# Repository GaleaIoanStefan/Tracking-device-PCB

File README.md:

# Project description

In this project i have designed and coded a shield for the STM32 Nucleo board L476RG.

The shield is the prototype of a tracker that will update the position using a GPS module and a LoRa modem for communication with a server.
The board is made to connect to the Orange LiveObjects server from which the data is put inside a MongoDB database and later a template is made in Grafana with the longitude and latitude coordinates.
Two Python scripts are present in the project. One for getting the data from the LiveObjects through MQTT protocol, and the other links the data received to a endpoint. That endpoint in later linked to a Grafana JSON plugin to gather that data.

The programming of the board was done in STM32CubeIDE and all communications between The GPS, Lora and COM port were UART communications.

# The Electrical Schematic

# The layout of the PCB

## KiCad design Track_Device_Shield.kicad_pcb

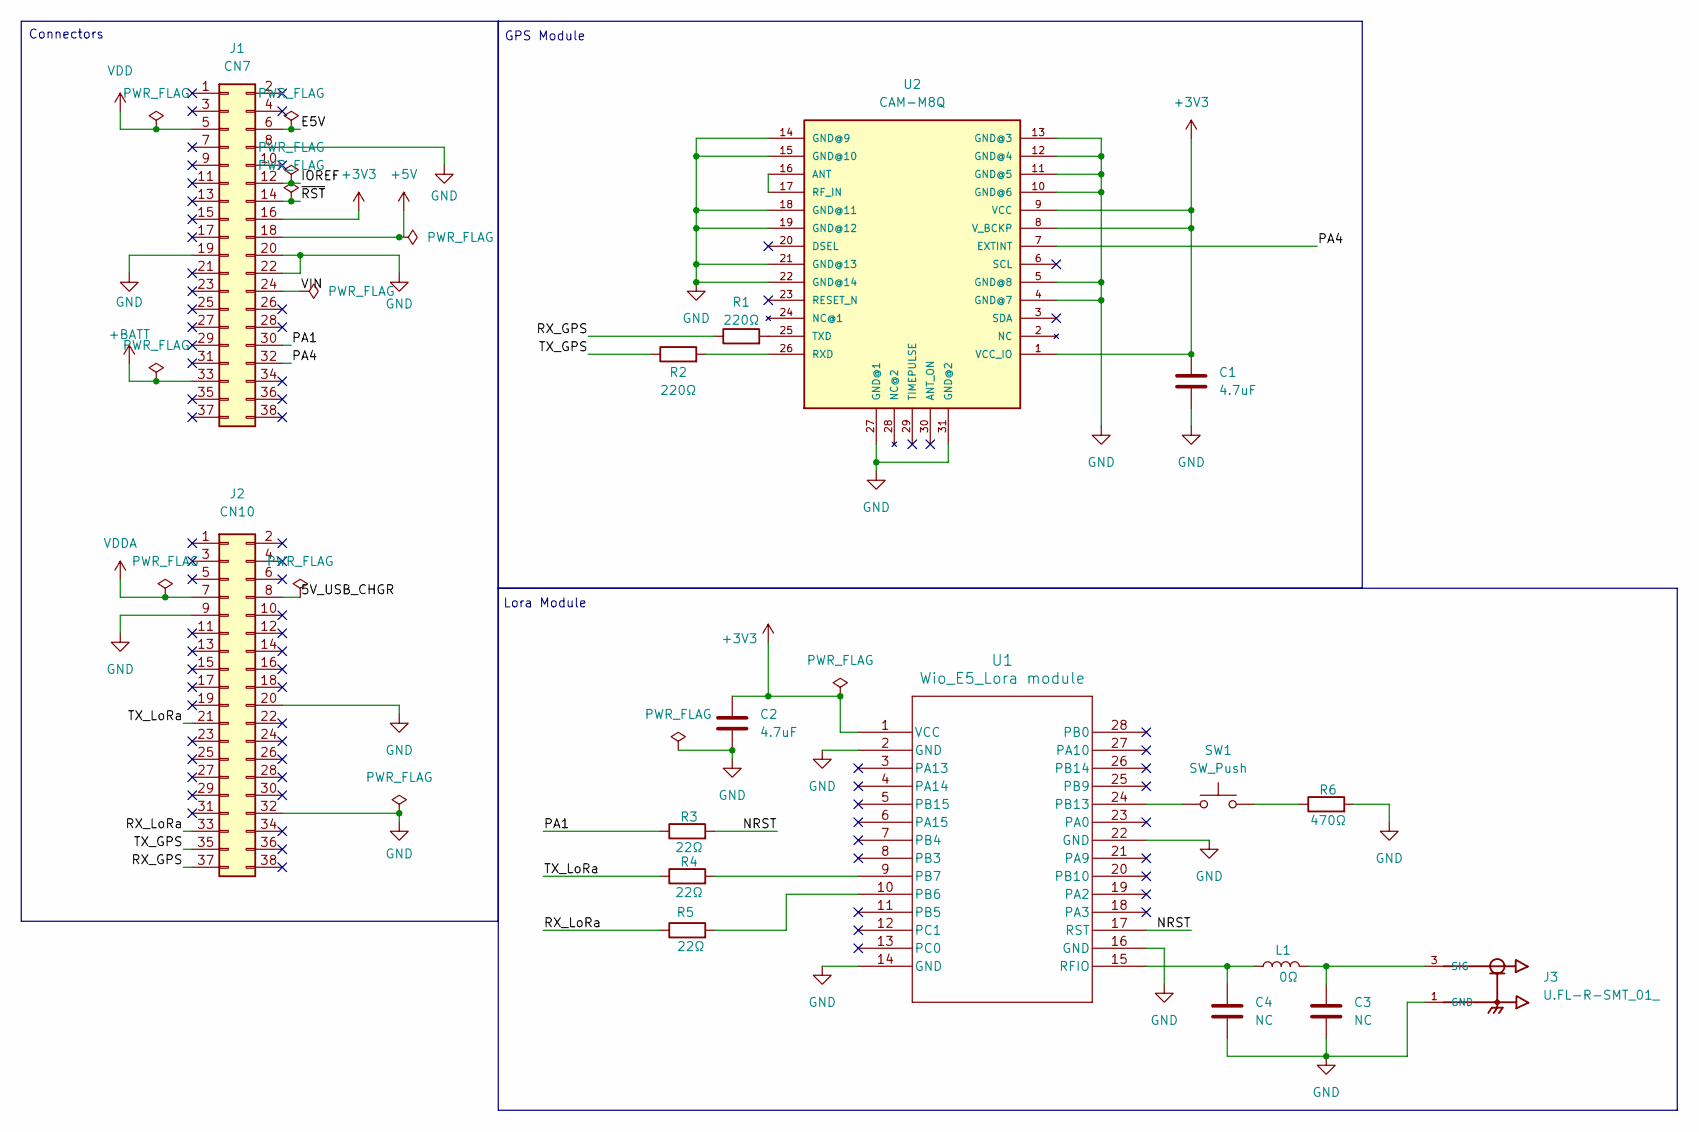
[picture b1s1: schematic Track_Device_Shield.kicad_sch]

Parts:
C1: 4.7uF; C_0805_2012Metric_Pad1.18x1.45mm_HandSolder
C2: 4.7uF; C_0805_2012Metric
C3, C4: NC; C_0805_2012Metric
J1: CN7; PinSocket_2x19_P2.54mm_Vertical
J2: CN10; PinSocket_2x19_P2.54mm_Vertical
J3: U.FL-R-SMT_01_; HRS_U.FL-R-SMT_01_
L1: 0Ω; L_0603_1608Metric
R1, R2: 220Ω; R_0603_1608Metric_Pad0.98x0.95mm_HandSolder
R3, R4, R5: 22Ω; R_0402_1005Metric
R6: 470Ω; R_0402_1005Metric
SW1: SW_Push; SW_PUSH_6mm
U1: Wio_E5_Lora module; Wio_E5_Lora module footprint
U2: CAM-M8Q; CAM-M8

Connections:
+3V3: C1.1, C2.1, J1.16, U1.1 (VCC), U2.1 (VCC_IO), U2.8 (V_BCKP), U2.9 (VCC)
+5V: J1.18
+BATT: J1.33
/5V_USB_CHGR: J2.8
/E5V: J1.6
/IOREF: J1.12
/NRST: R3.2, U1.17 (RST)
/PA1: J1.30, R3.1
/PA4: J1.32, U2.7 (EXTINT)
/RX_GPS: J2.37, R1.1
/RX_LoRa: J2.33, R5.1
/TX_GPS: J2.35, R2.1
/TX_LoRa: J2.21, R4.1
/VIN: J1.24
/~RST: J1.14
GND: C1.2, C2.2, C3.2, C4.2, J1.8, J1.19, J1.20, J1.22, J2.9, J2.20, J2.32, J3.1 (GND), J3.2 (GND), R6.2, U1.2 (GND), U1.14 (GND), U1.16 (GND), U1.22 (GND), U2.4 (GND@7), U2.5 (GND@8), U2.10 (GND@6), U2.11 (GND@5), U2.12 (GND@4), U2.13 (GND@3), U2.14 (GND@9), U2.15 (GND@10), U2.18 (GND@11), U2.19 (GND@12), U2.21 (GND@13), U2.22 (GND@14), U2.27 (GND@1), U2.31 (GND@2)
unnamed: C3.1, J3.3 (SIG), L1.2
unnamed: R6.1, SW1.2
unnamed: R5.2, U1.10 (PB6)
unnamed: R4.2, U1.9 (PB7)
unnamed: SW1.1, U1.24 (PB13)
unnamed: C4.1, L1.1, U1.15 (RFIO)
unnamed: U2.16 (ANT), U2.17 (RF_IN)
unnamed: R2.2, U2.26 (RXD)
unnamed: R1.2, U2.25 (TXD)
VDD: J1.5
VDDA: J2.7

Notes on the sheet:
Lora Module
GPS Module
Connectors

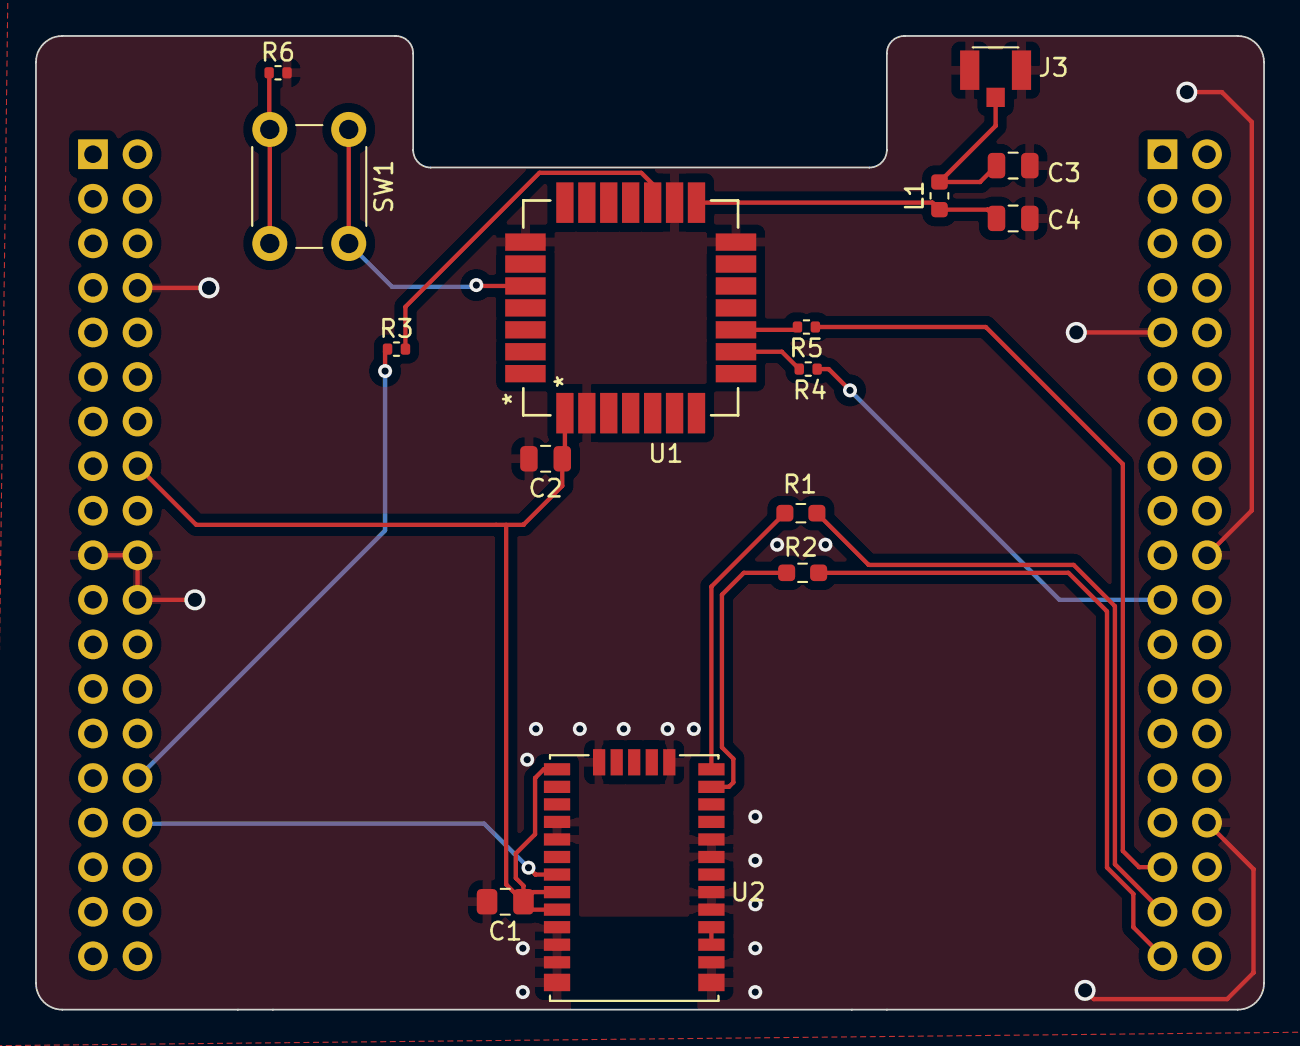
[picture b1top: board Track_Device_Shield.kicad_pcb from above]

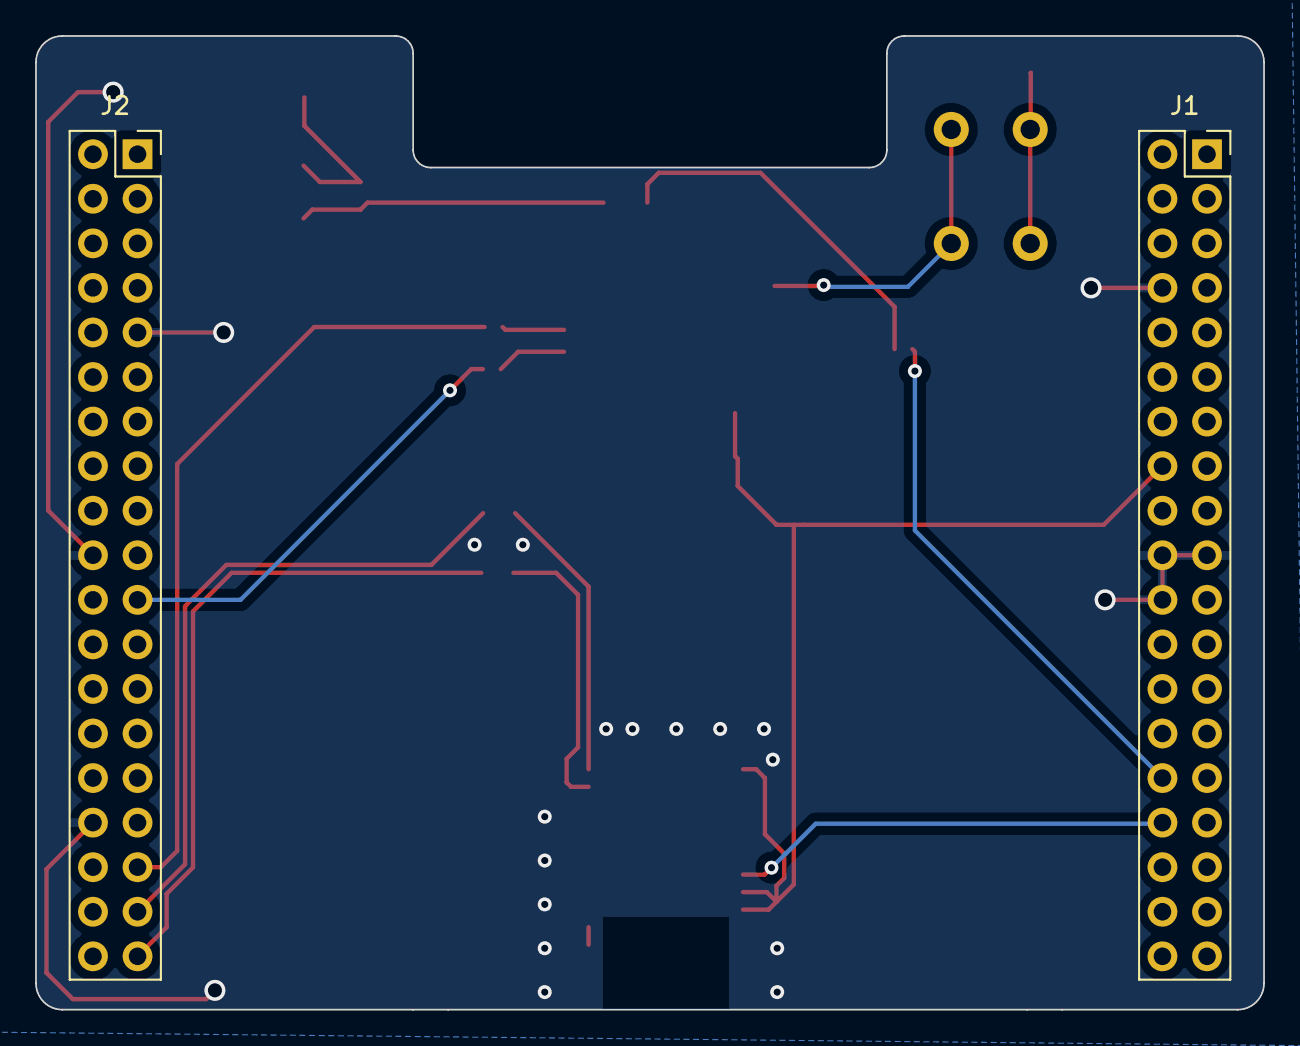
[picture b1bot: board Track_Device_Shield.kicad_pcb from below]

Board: 2 copper layers, 70.0 x 55.5 mm, 17 parts (2 on the bottom side), 18 nets.
